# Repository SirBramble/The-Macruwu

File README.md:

# The Macruwu
The macro pad for all! (well, at least, if you can understand the Clusterfuck posted here)
The Firmware is based on the Arduino Pico Core by earlephilhower https://github.com/earlephilhower/arduino-pico. 

**This is only a brief overview** The full documentation and instructions can be found in the "Documentation"-folder.

## Components used

I went with the RP2040 based board from seeed studio. It has a fast chip, offers integrated USB support and is only about 6€. However, it has limited GPIO pins. So if you want to build your own, I would recommend using I/O Expanders or something similar. Another option would be to use a raspberry Pi with a RP2040. This Board beaks out most of the RP2040 Pins and has Options for Wi-Fi.

In order to try out different Key switches and keep the Macruwu modular, I decided to use hot swap sockets. They aren’t to expensive, if you order them for AliExpress (about 1\$/10psc). But beware, when soldering. If your board manufacturer decides to give you the shit coating on your Pads, prepare for heavy flux use.

For the I/O Expanders I used the PCA9555 from NXP. They conveniently don’t need a lot of setup and are automatically set to INPUT_PULLUP. The detailed Addressing scheme and co can be found in the Datasheet. But, as per usual nowadays, the I/O expanders are sold out. So, you might want to look for them somewhere else, or find a suitable replacement. But if you can find them, I can recommend the NXP Expanders. They need minimal to no Software Setup and I haven't had a dead one so far.

The level shifter (TXU0104PWR) is a cheap option I got from Mouser. It has 4 channels it can shift and is enough for the two 5V I²C Lines and the neopixel line.

The keyswitches were purchased for AliExpress and some smaller Keyboard parts suppliers. I like clicky switches, so I went for the Gateron greens. However, I cannot recommend them. They sound quite hollow and scratchy. Could maybe fixed with some lube *gigidy*, but it’s not really worth the trouble. 
If you want some really clicky Keyswitches, that will any the hell out of anybody in a 30km Radius, you could go for the Kailh Low profile Chock whites. My, extremely pissed of, fellow student can confirm. However, be aware that they can not be used with relegendable keycaps.
## How to compile

### With the Arduino IDE 2.0
First download the Code either from the repo or via the release tab. Put it in a folder and open the ```Macruwu_OS.ino``` file.

In order to compile the Code, you need to install the Arduino Pico core. There is a Tutorial on how to do this on earlephilhowers GitHub. You will also need the Adafruit SPIFlash Library. It can be downloaded via the Library Manager. The rest should be included in the Pico Core.
If you get Library conflicts, I'm afraid you're on you’re own. I somehow got it to compile and haven’t touched my setup since. No Idea why it suddenly worked, but the only thing I can recommend, is to back up your libraries and start fresh.

EDIT: If you get a Library conflict, you may want to look for other Bugs. Sometimes the Arduino IDE shows this message, just to inform you, that it has used a certain Library. However, your Code may not compile due to another error.

Also remember to change the USB Stack to the Adafruit TinyUsb Stack via Tools->USB Stack.
If you want to use the inbuilt Flash as a drive, you also have to allocate Memory under Tools->Flash Size. The first time you allocate Memory, you will have to format it. Just doing it in Windows should be fine.
P.s. The flash drive code is more or less copied from Adafruit. sorry, I was lazy...

### With PlatformIO
Well... I have no Idea, but let me know, if you find out.

## How to use (isch...)

The Macruwu OS is divided in to several Files for maximum ```'someFuckingShit' is not defined did you mean 'goFuckYourself'?```

### With macroLayout.txt

NOTE: The first time you start the Macruwu, you might have problem, with it crashing. This may be caused by the File not being present in the Flash directory. You may have to disable the ```readFile```-function in the ```Keyboard::init```-function in ```Keyboard.cpp``` and upload the File first. Then reenable the function and it should run.

The Layout can be set with several Commands. ```Layer x: ``` sets the Layer under which the Buttons will be accessible. ```Button x: {string}``` sets the Button and is followed by the string, that will be printed by the keyboard. Remember to leave a space between ```:``` and ```{string}```. This is due to the way that the file gets read. The Character straight after the ```:``` will be ignored.

So far, most characters will be interpreted correctly, however ```<``` and ```>``` have a special Meaning. They press the left and right arrow keys respectively. Verry useful for Macro pads that print code with a lot of Brackets. Other functions have not yet been implemented, but feel free to add them in the ```Keyboard.cpp``` under ```Keyboard::interpet```.

In order to read the file from the Flash in to the Data structure you want to run the ```readFile```-function at least once. I recommend running it once in ```setup()``` and then running it each time the file is changed. this can be done with:
```
if(Macruwu.fsChanged()){
    Macruwu.readFile();
  }
```

In order to run the commands that have been set in the Data structure you will have to run the ```interpret(layer, button)```-function.

### With Hardcoded Mapping
The Keymapping can be set in the ```Mapping.cpp```.

In order to write something over USB, you can use ```Keyboard1.write("something");``` But this only works for most normal characters like letters and sometimes other specialty symbols. You'll have to try it out. Things like Brackets or things that use function keys, will have to be set up manually. This can either be done, by sending the commands via the Tiny USB library directly, or by adding a new function to the Keyboard class. But look through the Keyboard class, as I may add more functions in the future.

**Word of Warning:** If you do not have a US Keyboard, be prepared for some HID Code treasure hunting. I haven’t found a way to change the layout, so you either have to find a Layout and redefine all the keys in the library, or just try and hope you find what you need. If you have a German Keyboard layout set, you can reference the code for some mappings.

## Bugs
Yes

## Further documentation
I recommend reading the documentation by earlephilhower https://github.com/earlephilhower/arduino-pico. It´s a far better than this clusterfuck, but feel free to look through the code.

And in case you didn't read the first 3 lines, you can find more documentation in the "Documentation"-folder.

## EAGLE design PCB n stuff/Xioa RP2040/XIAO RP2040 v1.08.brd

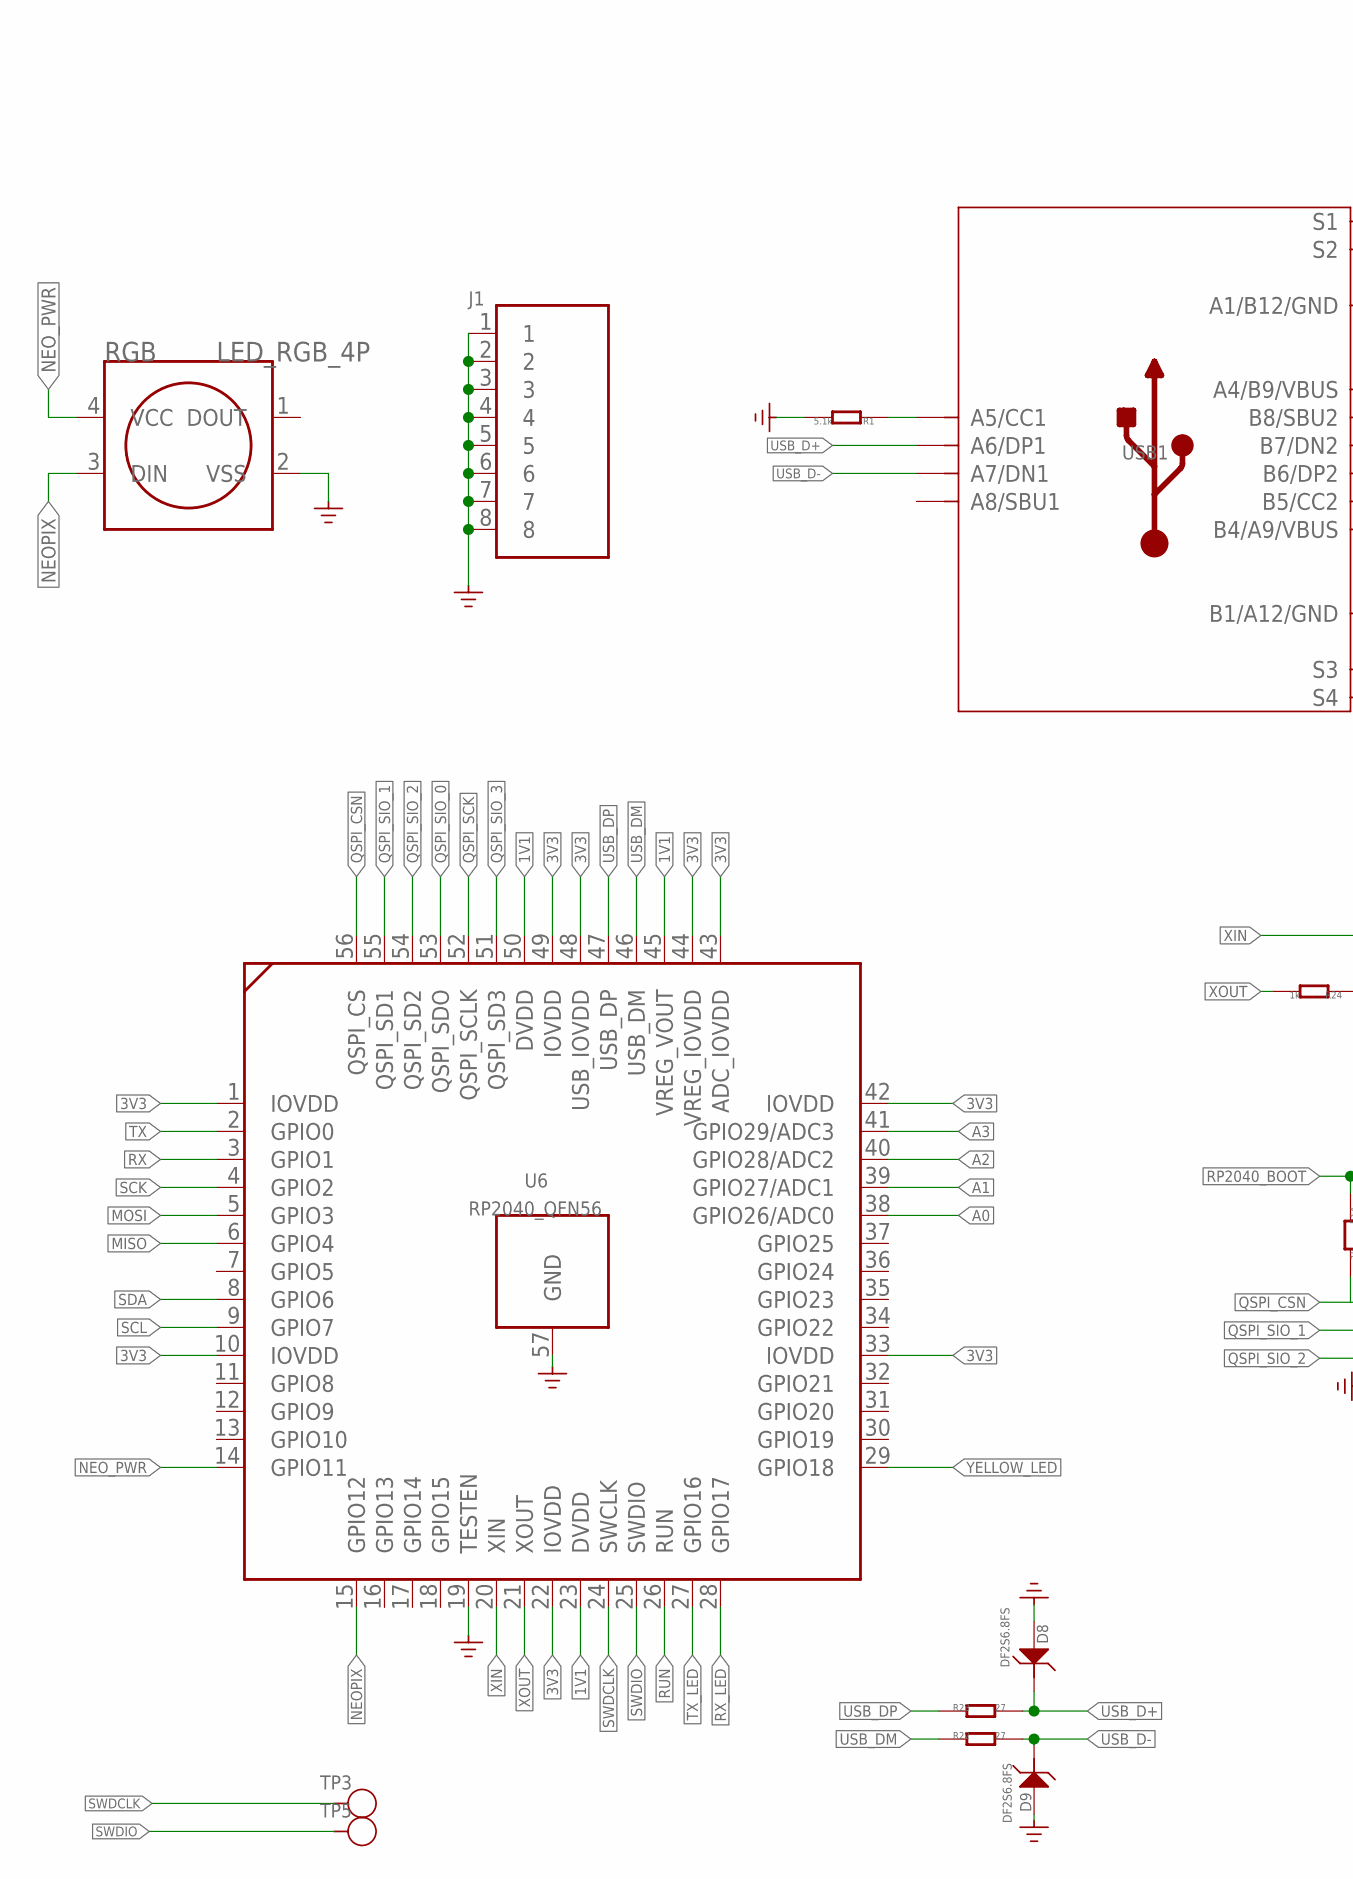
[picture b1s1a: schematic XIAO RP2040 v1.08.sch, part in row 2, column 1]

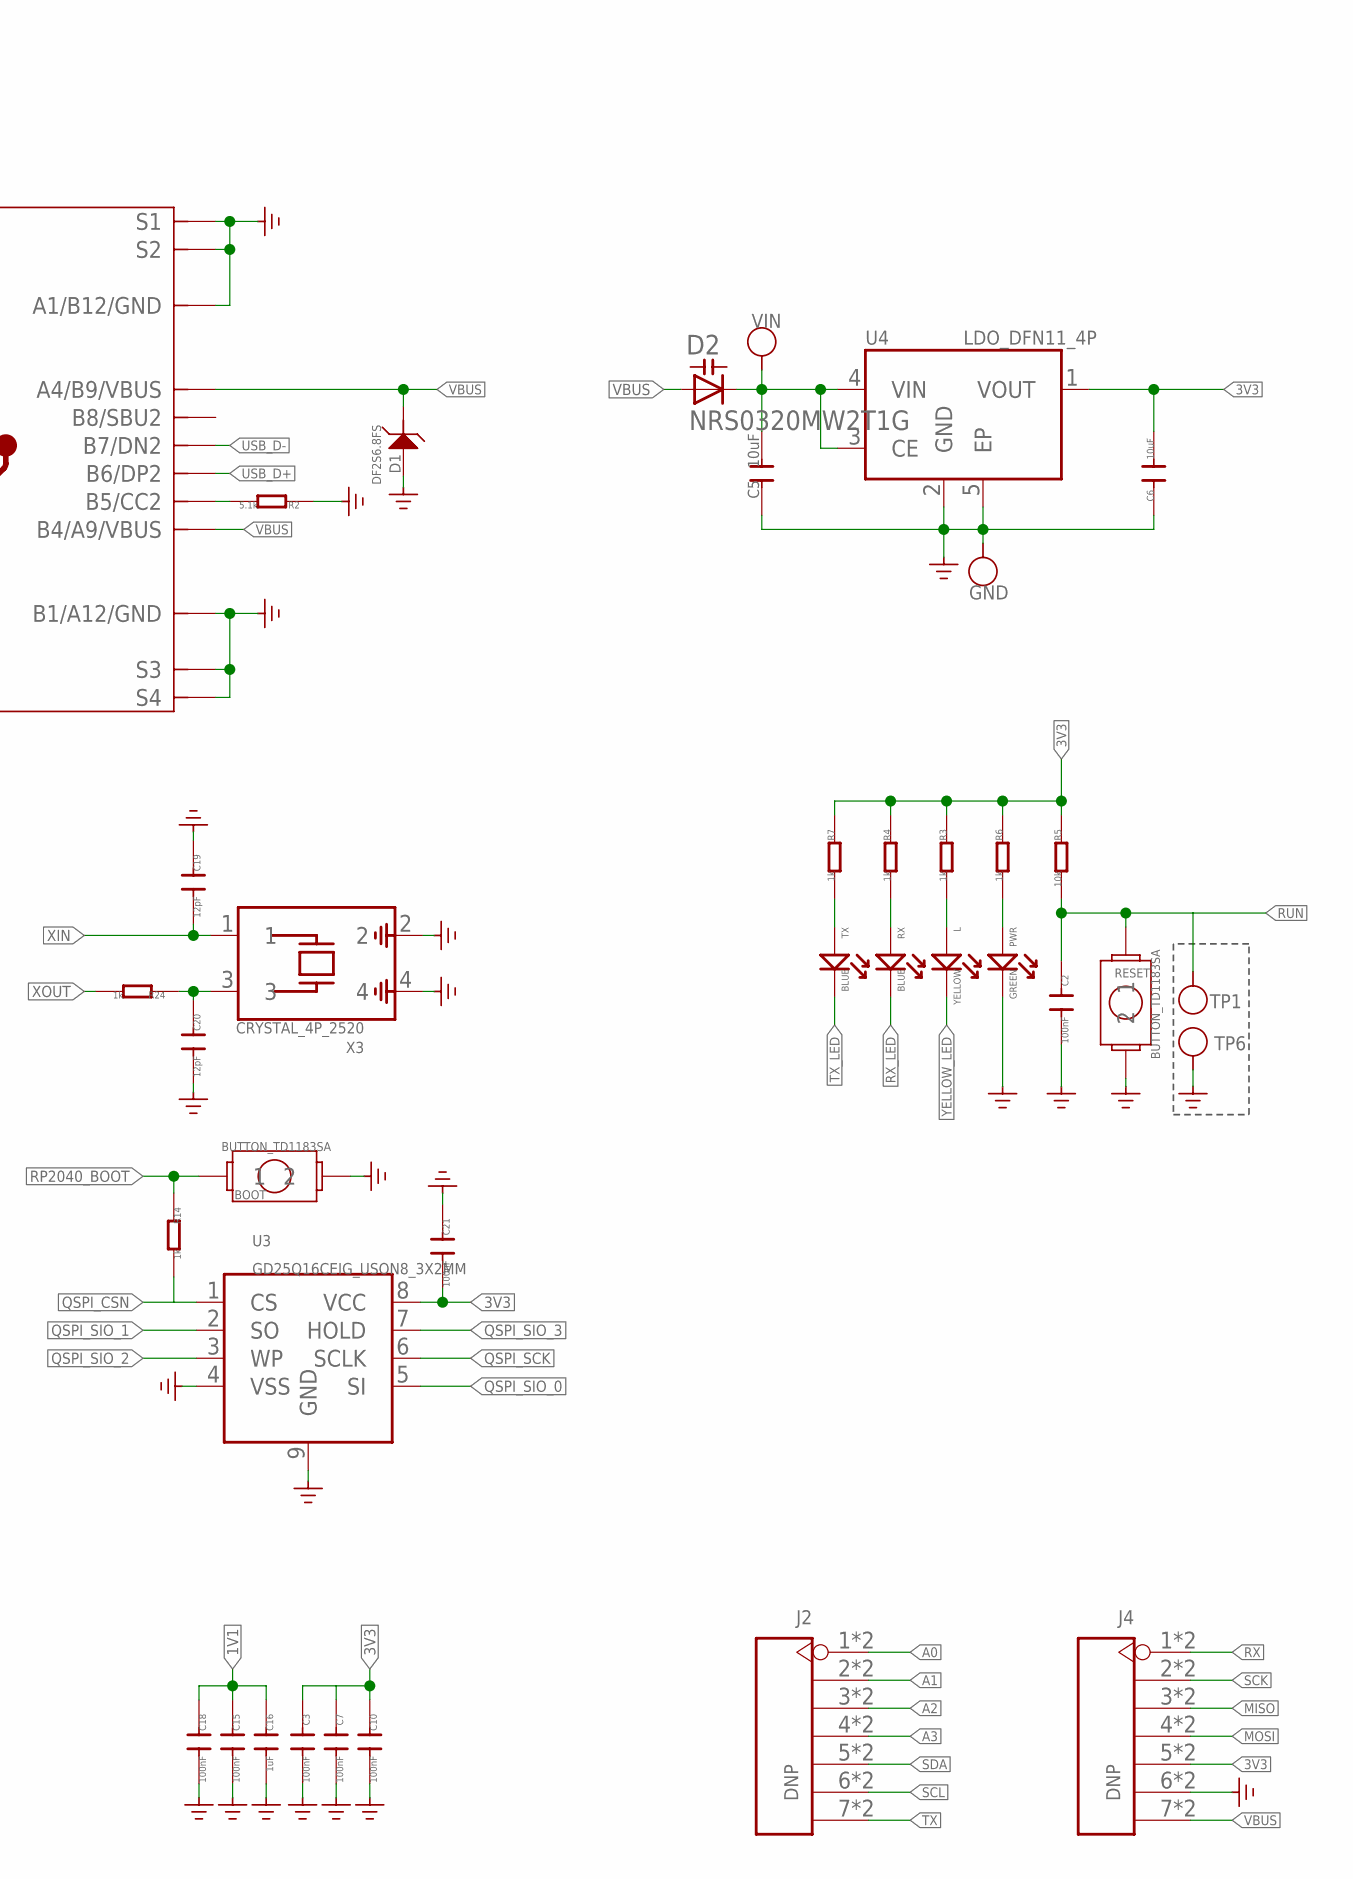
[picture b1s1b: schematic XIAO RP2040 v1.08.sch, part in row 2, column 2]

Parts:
BOOT: BUTTON_TD1183SA
C2, C3, C7, C10, C15, C18, C21: 100nF; 0201_NORMAL\NOSILK
C5, C6: 10uF; C0402
C16: 1uF; 0201_NORMAL\NOSILK
C19, C20: 12pF; 0201_NORMAL\NOSILK
D1, D8, D9: DF2S6.8FS; SOD-923
D2: NRS0320MW2T1G; SOD523
GND: TEST-POINT'4080'; TP-80X40MIL
J1: SHIELDING-COVER-XIAO_RP2040_PRD; SHIELDING-COVER_XIAO_RP2040_PRD
J2, J4: DNP; H7-HALF-HOLE-2.54
L: YELLOW; LED-0402
PWR: GREEN; LED-0402
R1, R2: 5.1k; R0201
R3, R4, R6, R7, R14, R24: 1k; R0201
R5: 10k; R0201
R22, R23: 27; R0201
RESET: BUTTON_TD1183SA
RGB: LED_RGB_4P; LED_RGB_2427
RX: BLUE; LED-0402
TP1, TP3, TP5, TP6: TEST-POINT'4545'; TP-D45MIL
TX: BLUE; LED-0402
U3: GD25Q16CEIG_USON8_3X2MM
U4: LDO_DFN11_4P; LDO_DFN1*1_4P
U6: RP2040_QFN56
USB1: USB2.0-TYPE-C
VIN: TEST-POINT'4080'; TP-80X40MIL
X3: CRYSTAL_4P_2520

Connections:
1V1: C15.1, C16.1, C18.1, U6.23 (DVDD), U6.45 (VREG_VOUT), U6.50 (DVDD)
3V3: C3.1, C6.2, C7.1, C10.1, C21.2, J4.5, J4.17 (5), R3.1, R4.1, R5.1, R6.1, R7.1, U3.8 (VCC), U4.1 (VOUT), U6.1 (IOVDD), U6.10 (IOVDD), U6.22 (IOVDD), U6.33 (IOVDD), U6.42 (IOVDD), U6.43 (ADC_IOVDD), U6.44 (VREG_IOVDD), U6.48 (USB_IOVDD), U6.49 (IOVDD)
A0: J2.1, J2.13 (1), U6.38 (GPIO26/ADC0)
A1: J2.2, J2.14 (2), U6.39 (GPIO27/ADC1)
A2: J2.3, J2.15 (3), U6.40 (GPIO28/ADC2)
A3: J2.4, J2.16 (4), U6.41 (GPIO29/ADC3)
GND: BOOT.2, C2.2, C3.2, C5.1, C6.1, C7.2, C10.2, C15.2, C16.2, C18.2, C19.1, C20.2, C21.1, D1.2 (1), D8.2 (1), D9.2 (1), GND.1, J1.1, J1.2, J1.3, J1.4, J1.5, J1.6, J1.7, J1.8, J4.6, J4.18 (6), PWR.-, R1.2, R2.1, RESET.2, RGB.2 (VSS), TP6.T, U3.4 (VSS), U3.9 (GND), U4.2 (GND), U4.5 (EP), U6.19 (TESTEN), U6.57 (GND), USB1.A1_B12 (A1/B12/GND), USB1.B1_A12 (B1/A12/GND), USB1.S1, USB1.S2, USB1.S3, USB1.S4, USB1.S5 (S1), USB1.S6 (S2), X3.2, X3.4
MISO: J4.3, J4.15 (3), U6.6 (GPIO4)
MOSI: J4.4, J4.16 (4), U6.5 (GPIO3)
unnamed: R1.1, USB1.A5 (A5/CC1)
unnamed: R2.2, USB1.B5 (B5/CC2)
unnamed: L.+, R3.2
unnamed: R7.2, TX.+
unnamed: C20.1, R24.1, X3.3
unnamed: R4.2, RX.+
unnamed: PWR.+, R6.2
NEOPIX: RGB.3 (DIN), U6.15 (GPIO12)
NEO_PWR: RGB.4 (VCC), U6.14 (GPIO11)
QSPI_CSN: R14.2, U3.1 (CS), U6.56 (QSPI_CS)
QSPI_SCK: U3.6 (SCLK), U6.52 (QSPI_SCLK)
QSPI_SIO_0: U3.5 (SI), U6.53 (QSPI_SDO)
QSPI_SIO_1: U3.2 (SO), U6.55 (QSPI_SD1)
QSPI_SIO_2: U3.3 (WP), U6.54 (QSPI_SD2)
QSPI_SIO_3: U3.7 (HOLD), U6.51 (QSPI_SD3)
RP2040_BOOT: BOOT.1, R14.1
RUN: C2.1, R5.2, RESET.1, TP1.T, U6.26 (RUN)
RX: J4.1, J4.13 (1), U6.3 (GPIO1)
RX_LED: RX.-, U6.28 (GPIO17)
SCK: J4.2, J4.14 (2), U6.4 (GPIO2)
SCL: J2.6, J2.18 (6), U6.9 (GPIO7)
SDA: J2.5, J2.17 (5), U6.8 (GPIO6)
SWDCLK: TP3.T, U6.24 (SWCLK)
SWDIO: TP5.T, U6.25 (SWDIO)
TX: J2.7, J2.19 (7), U6.2 (GPIO0)
TX_LED: TX.-, U6.27 (GPIO16)
USB_D+: D8.1 (2), R23.2, USB1.A6 (A6/DP1), USB1.B6 (B6/DP2)
USB_D-: D9.1 (2), R22.2, USB1.A7 (A7/DN1), USB1.B7 (B7/DN2)
USB_DM: R22.1, U6.46 (USB_DM)
USB_DP: R23.1, U6.47 (USB_DP)
VBUS: D1.1 (2), D2.A, J4.7, J4.19 (7), USB1.A4_B9 (A4/B9/VBUS), USB1.B4_A9 (B4/A9/VBUS)
VIN: C5.2, D2.C, U4.3 (CE), U4.4 (VIN), VIN.1
XIN: C19.2, U6.20 (XIN), X3.1
XOUT: R24.2, U6.21 (XOUT)
YELLOW_LED: L.-, U6.29 (GPIO18)

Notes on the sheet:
2021.5.18
zhihuai.zhou
v1.0
Initail Version

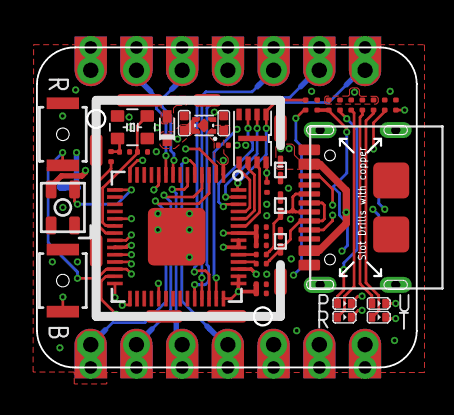
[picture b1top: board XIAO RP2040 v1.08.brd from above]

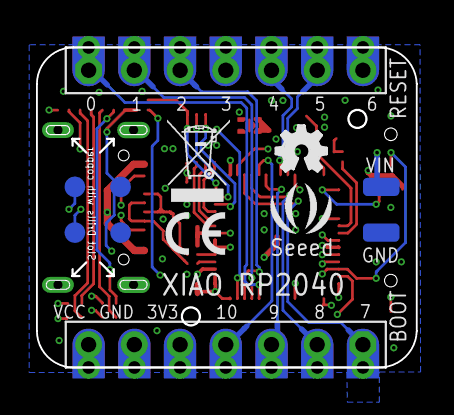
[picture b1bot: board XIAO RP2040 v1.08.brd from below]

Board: 4 copper layers, 21.1 x 17.8 mm, 50 parts (8 on the bottom side), 44 nets.

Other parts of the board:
U$4: OSHW_FILLX100_NOTEXT
U$6: SEEED-SILK--TNAME-160*153MIL

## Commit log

2022-10-17 added README
2022-10-17 added OS
2022-10-28 first release
2022-10-28 changed README
2022-12-08 working backup #2
2022-12-10 Backup with Serial prints for debugging
2022-12-10 added Filereadin
2022-12-10 removed flash.ino.old
2022-12-11 fixed some bugs and added comments
2022-12-11 updated 3D moddels
2022-12-12 fixed body to fit MX hotswap sockets
2023-01-06 major update
2023-01-06 updated 3D models
2023-01-11 minor cleanup
2023-01-15 fixed spelling
2023-02-06 started documentation in I2C
